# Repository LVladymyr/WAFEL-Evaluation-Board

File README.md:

# WAFEL EVAL BOARD

**Version:** 0.0.1

Evaluation board for the [Texas Instruments BQ76952](https://www.ti.com/product/BQ76952) multi-chemistry battery management IC. Designed to prototype and validate BMS firmware, cell monitoring, and protection circuits.

## Features

- BQ76952 multi-chemistry BMS IC (up to 16S, supports Li-ion, LiFePO4, NiMH)
- LM5164 synchronous buck regulator for on-board power supply
- TPS79333-EP ultra-low-noise LDO
- Charge and discharge MOSFET control path
- Automotive-grade blade fuse holder
- JST GH 17-pin battery connector
- Test points on key signals for bench debugging
- CI/CD pipeline: Gerbers, BOM, PDF schematic, 3D STEP, interactive BOM (iBOM)

## Hardware Overview

| Component | Part | Role |
|-----------|------|------|
| BMS IC | BQ76952 | Cell voltage/temperature monitoring, balancing, protection |
| Buck regulator | LM5164 | Steps down pack voltage to board supply rail |
| LDO | TPS79333-EP | Clean analog/digital supply from buck output |
| Charge FETs | — | Controlled by BQ76952 CHG/DSG pins |
| Connector | JST GH 17-pin | Battery pack interface |
| Fuse | Automotive blade | Pack-level overcurrent protection |

## Repository Structure

```
WAFEL_EVAL_BOARD/
├── *.kicad_pro        # KiCad project file
├── *.kicad_sch        # Schematic
├── *.kicad_pcb        # PCB layout
├── *.kicad_dru        # Design rules
├── fp-lib-table       # Footprint library table
├── sym-lib-table      # Symbol library table
├── .github/
│   └── workflows/     # CI/CD pipeline (KiBot)
└── README.md
```

## CI/CD & Manufacturing Outputs

Commits to `main` trigger a [KiBot](https://github.com/INTI-CMNB/KiBot) workflow via GitHub Actions that automatically generates:

- **Gerbers** — production-ready fabrication files
- **BOM** — bill of materials (CSV)
- **PDF** — schematic and PCB drawings
- **3D STEP** — mechanical model for enclosure design
- **iBOM** — interactive HTML BOM for assembly

Artifacts are attached to each workflow run.

## Getting Started

1. Install [KiCad 9.0](https://www.kicad.org/download/)
2. Clone this repository
3. Open the `.kicad_pro` file in KiCad

## License

Hardware design files are licensed under the **CERN Open Hardware Licence Version 2 – Strongly Reciprocal (CERN-OHL-S v2)**.
See [https://ohwr.org/cern_ohl_s_v2.txt](https://ohwr.org/cern_ohl_s_v2.txt) for the full license text.

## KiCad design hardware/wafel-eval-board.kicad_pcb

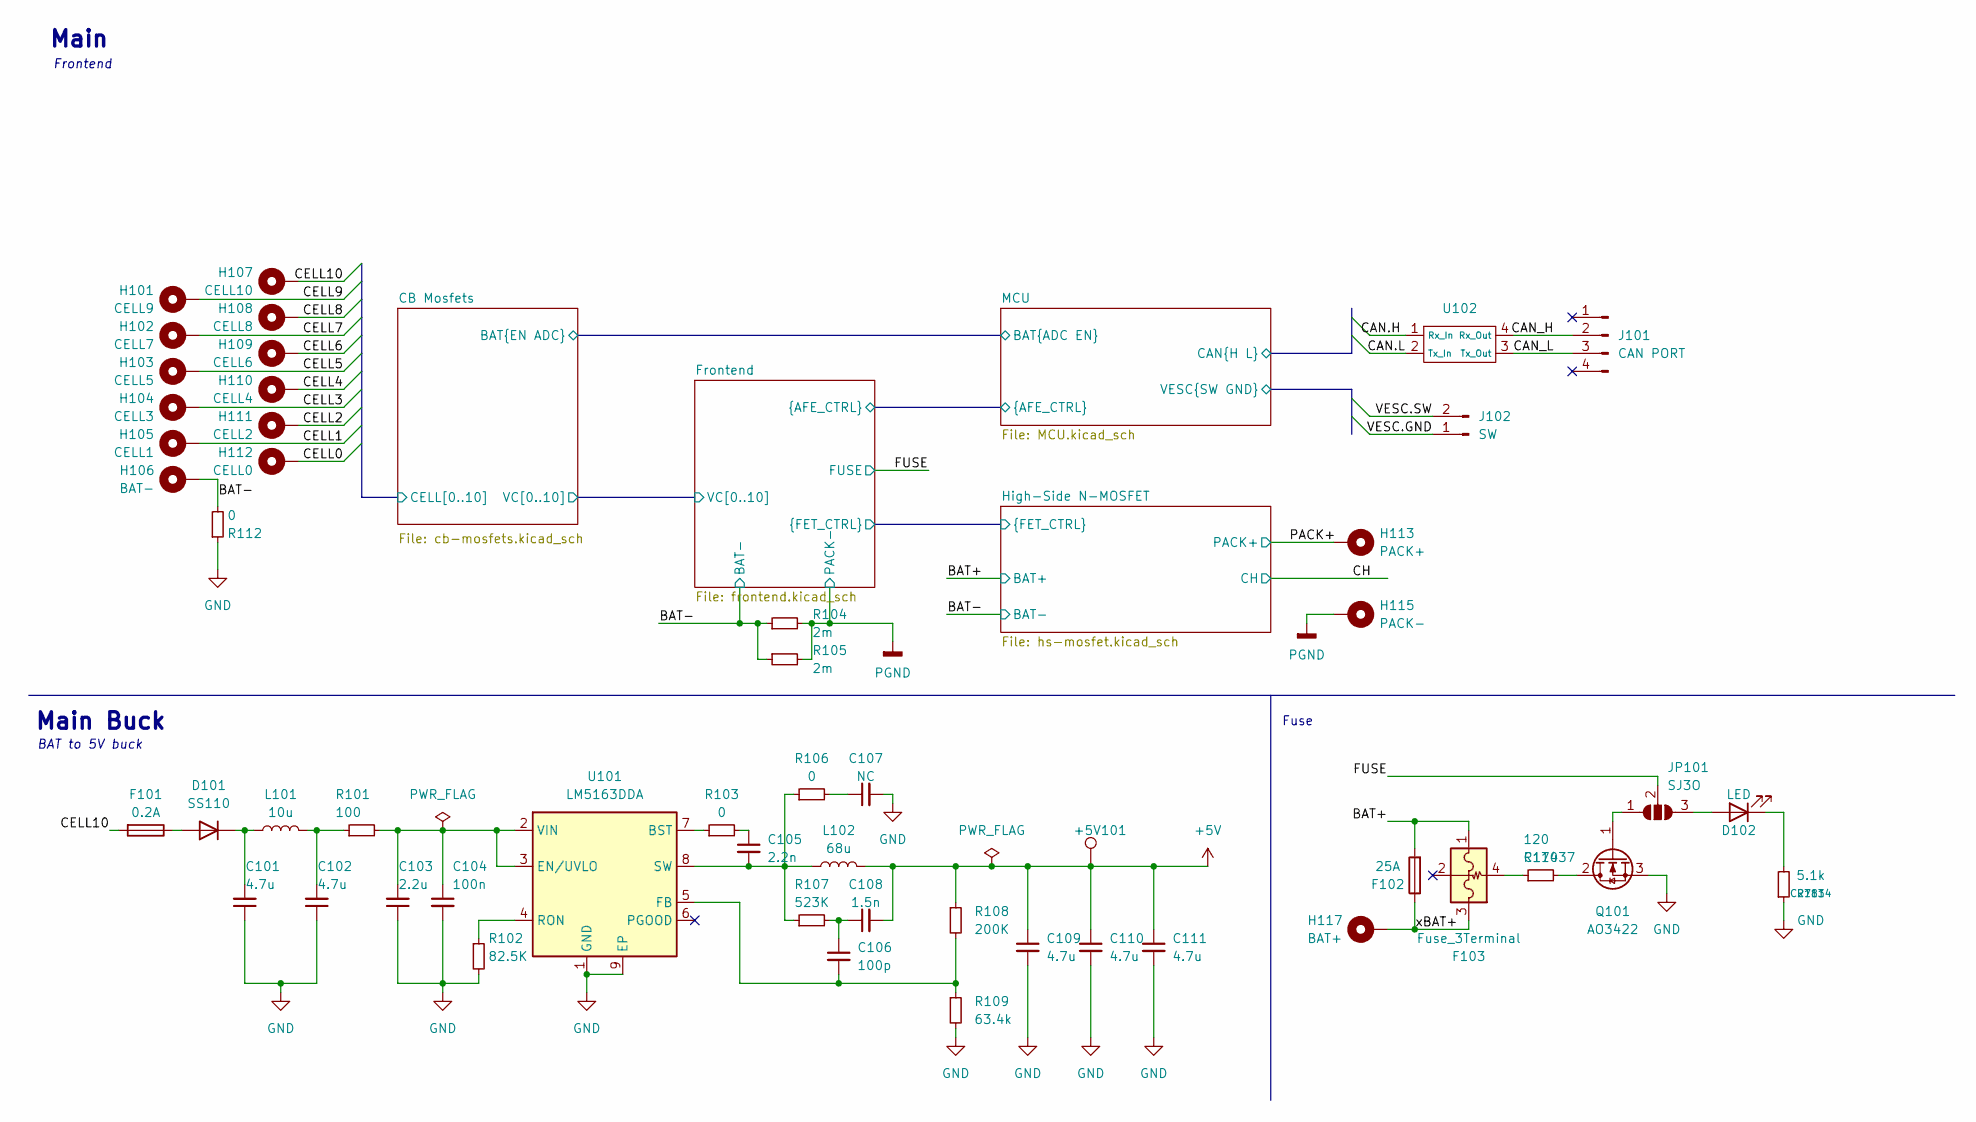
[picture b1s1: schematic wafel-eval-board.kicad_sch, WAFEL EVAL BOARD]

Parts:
+5V101: TestPoint; TestPoint_Pad_D1.0mm
C101, C102, C109, C110, C111: 4.7u; C_1206_3216Metric; LCSC C577211
C103: 2.2u; C_1206_3216Metric; LCSC C577211
C104: 100n; C_1206_3216Metric; LCSC C1945
C105: 2.2n; C_0603_1608Metric; LCSC C106861
C106: 100p; C_0603_1608Metric
C107: NC; C_0603_1608Metric
C108: 1.5n; C_0603_1608Metric
D101: SS110; D_SMA; LCSC C18199178
D102: LED; LED_0201_0603Metric
F101: 0.2A; Fuse_Littelfuse-NANO2-451_453; LCSC C178980
F102: 25A; Fuse_Littelfuse-NANO2-451_453; LCSC C178980
F103: Fuse_3Terminal; Fuse_ITV5432
H101: CELL9; MountingHole_3.2mm_M3_Pad
H102: CELL7; MountingHole_3.2mm_M3_Pad
H103: CELL5; MountingHole_3.2mm_M3_Pad
H104: CELL3; MountingHole_3.2mm_M3_Pad
H105: CELL1; MountingHole_3.2mm_M3_Pad
H106: BAT-; MountingHole_3.2mm_M3_Pad
H107: CELL10; MountingHole_3.2mm_M3_Pad
H108: CELL8; MountingHole_3.2mm_M3_Pad
H109: CELL6; MountingHole_3.2mm_M3_Pad
H110: CELL4; MountingHole_3.2mm_M3_Pad
H111: CELL2; MountingHole_3.2mm_M3_Pad
H112: CELL0; MountingHole_3.2mm_M3_Pad
H113: PACK+; MountingHole_3.2mm_M3_Pad
H115: PACK-; MountingHole_3.2mm_M3_Pad
H117: BAT+; MountingHole_3.2mm_M3_Pad
J101: CAN PORT; JST_PH_S4B-PH-K_1x04_P2.00mm_Horizontal
J102: SW; JST_PH_S2B-PH-K_1x02_P2.00mm_Horizontal
JP101: SJ3O; SolderJumper-3_P1.3mm_Open_Pad1.0x1.5mm
L101: 10u; L_KOHERelec_MDA7030; LCSC C2894721
L102: 68u; L_KOHERelec_MDA7030; LCSC C2894721
Q101: AO3422; SOT-23
R101: 100; R_0603_1608Metric; LCSC C17408
R102: 82.5K; R_0603_1608Metric; LCSC C3013228
R103: 0; R_0603_1608Metric; LCSC C17477
R104, R105: 2m; R_2512_6332Metric
R106, R112: 0; R_0603_1608Metric
R107: 523K; R_0603_1608Metric; LCSC C17742
R108: 200K; R_0603_1608Metric; LCSC C17539
R109: 63.4k; R_0603_1608Metric; LCSC C49654429
R110: 120; R_0603_1608Metric; LCSC C17437
R111: 5.1k; R_0603_1608Metric; LCSC C27834
U101: LM5163DDA; HSOP-8-1EP_3.9x4.9mm_P1.27mm_EP2.41x3.1mm_ThermalVias; LCSC C2873264
U102: poka-yoke_rxtx

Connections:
+5V: +5V101.1 (1_1), C108.2, C109.1, C110.1, C111.1, L102.2, R108.1; also elsewhere on the board
/BAT+: F102.2, F103.1; also elsewhere on the board
/BAT-: H106.1 (1_1), R104.1, R105.1, R112.2; also elsewhere on the board
/CAN_H: J101.2, U102.4 (Rx_Out)
/CAN_L: J101.3, U102.3 (Tx_Out)
/CB Mosfets/CELL0: H112.1 (1_1); also elsewhere on the board
/CB Mosfets/CELL1: H105.1 (1_1); also elsewhere on the board
/CB Mosfets/CELL2: H111.1 (1_1); also elsewhere on the board
/CB Mosfets/CELL3: H104.1 (1_1); also elsewhere on the board
/CB Mosfets/CELL4: H110.1 (1_1); also elsewhere on the board
/CB Mosfets/CELL5: H103.1 (1_1); also elsewhere on the board
/CB Mosfets/CELL6: H109.1 (1_1); also elsewhere on the board
/CB Mosfets/CELL7: H102.1 (1_1); also elsewhere on the board
/CB Mosfets/CELL8: H108.1 (1_1); also elsewhere on the board
/CB Mosfets/CELL9: H101.1 (1_1); also elsewhere on the board
/CB Mosfets/CELL10: F101.2, H107.1 (1_1); also elsewhere on the board
/FUSE: JP101.2 (C); also elsewhere on the board
/MCU/CAN.H: U102.1 (Rx_In); also elsewhere on the board
/MCU/CAN.L: U102.2 (Tx_In); also elsewhere on the board
/MCU/VESC.GND: J102.1; also elsewhere on the board
/MCU/VESC.SW: J102.2; also elsewhere on the board
/PACK+: H113.1 (1_1); also elsewhere on the board
/xBAT+: F102.1, F103.3, H117.1 (1_1)
GND: C101.1, C102.1, C103.1, C104.2, C107.2, C109.2, C110.2, C111.2, Q101.3 (S), R102.2, R109.2, R111.1, R112.1, U101.1 (GND), U101.9 (EP); also elsewhere on the board
unnamed: C102.2, L101.2, R101.1
unnamed: C105.1, R103.2
unnamed: C106.1, C108.1, R107.2
unnamed: C107.1, R106.2
unnamed: D101.2 (A), F101.1
unnamed: C101.2, D101.1 (K), L101.1
unnamed: D102.2 (A), JP101.3 (B)
unnamed: D102.1 (K), R111.2
unnamed: F103.4, R110.1
unnamed: JP101.1 (A), Q101.1 (G)
unnamed: Q101.2 (D), R110.2
unnamed: R103.1, U101.7 (BST)
unnamed: C103.2, C104.1, R101.2, U101.2 (VIN), U101.3 (EN/UVLO)
unnamed: C106.2, R108.2, R109.1, U101.5 (FB)
unnamed: R102.1, U101.4 (RON)
unnamed: C105.2, L102.1, R106.1, R107.1, U101.8 (SW)
PGND: H115.1 (1_1), R104.2, R105.2; also elsewhere on the board

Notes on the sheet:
Fuse
BAT to 5V buck
Frontend
Main Buck
Main

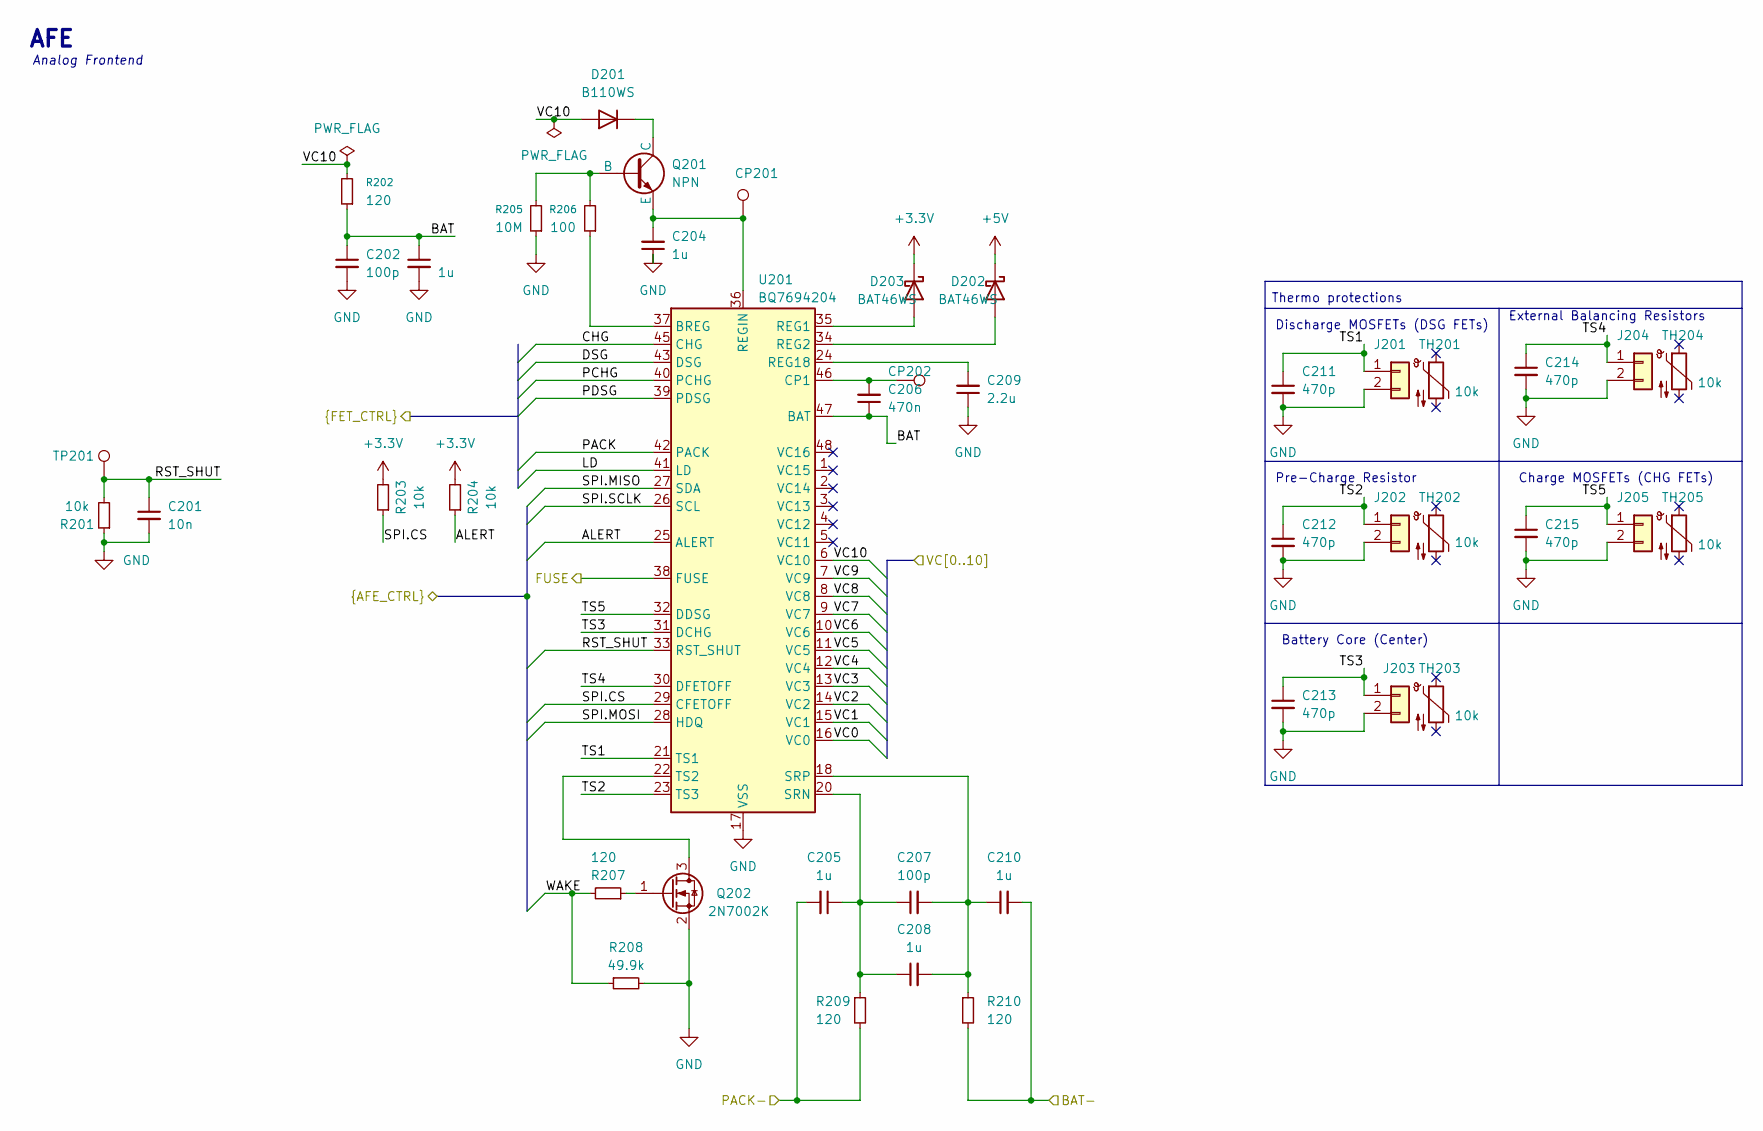
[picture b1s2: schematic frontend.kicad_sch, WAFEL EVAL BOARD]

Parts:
C201: 10n; C_0603_1608Metric
C202, C207: 100p; C_0603_1608Metric
C203: 1u; C_1206_3216Metric
C204, C205, C208, C210: 1u; C_0603_1608Metric
C206: 470n; C_0603_1608Metric
C209: 2.2u; C_1206_3216Metric; LCSC C577211
C211, C212, C213, C214, C215: 470p; C_0603_1608Metric
CP201, CP202: TestPoint; TestPoint_Pad_D1.0mm
D201: B110WS; D_SOD-323; LCSC C7461125
D202, D203: BAT46WS; D_SOD-323; LCSC C7502692
J201, J202, J203, J204, J205: Conn_01x02; PinHeader_1x02_P1.27mm_Vertical
Q201: NPN; SOT-23; Manufacturer_Part_Number FMMT458TA; Mouser Part Number 522-FMMT458TA
Q202: 2N7002K; SOT-23
R201, R203, R204: 10k; R_0603_1608Metric
R202, R207, R209, R210: 120; R_0603_1608Metric
R205: 10M; R_0603_1608Metric
R206: 100; R_0603_1608Metric
R208: 49.9k; R_0603_1608Metric
TH201, TH202, TH203, TH204, TH205: 10k; R_0603_1608Metric; LCSC C84036
TP201: TestPoint; TestPoint_Pad_D1.0mm
U201: BQ7694204; TQFP-48_7x7mm_P0.5mm

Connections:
+3.3V: D203.1 (K), R203.2, R204.2; also elsewhere on the board
+5V: D202.1 (K); also elsewhere on the board
/BAT-: C210.2, R210.2; also elsewhere on the board
/CB Mosfets/VC0: U201.16 (VC0); also elsewhere on the board
/CB Mosfets/VC1: U201.15 (VC1); also elsewhere on the board
/CB Mosfets/VC2: U201.14 (VC2); also elsewhere on the board
/CB Mosfets/VC3: U201.13 (VC3); also elsewhere on the board
/CB Mosfets/VC4: U201.12 (VC4); also elsewhere on the board
/CB Mosfets/VC5: U201.11 (VC5); also elsewhere on the board
/CB Mosfets/VC6: U201.10 (VC6); also elsewhere on the board
/CB Mosfets/VC7: U201.9 (VC7); also elsewhere on the board
/CB Mosfets/VC8: U201.8 (VC8); also elsewhere on the board
/CB Mosfets/VC9: U201.7 (VC9); also elsewhere on the board
/CB Mosfets/VC10: D201.2 (A), R202.2, U201.6 (VC10); also elsewhere on the board
/FUSE: U201.38 (FUSE); also elsewhere on the board
/Frontend/ALERT: R204.1, U201.25 (ALERT); also elsewhere on the board
/Frontend/BAT: C202.1, C203.1, C206.1, R202.1, U201.47 (BAT)
/Frontend/CHG: U201.45 (CHG); also elsewhere on the board
/Frontend/DSG: U201.43 (DSG); also elsewhere on the board
/Frontend/LD: U201.41 (LD); also elsewhere on the board
/Frontend/PACK: U201.42 (PACK); also elsewhere on the board
/Frontend/PCHG: U201.40 (PCHG); also elsewhere on the board
/Frontend/PDSG: U201.39 (PDSG); also elsewhere on the board
/Frontend/RST_SHUT: C201.1, R201.2, TP201.1 (1_1), U201.33 (RST_SHUT); also elsewhere on the board
/Frontend/SPI.CS: R203.1, U201.29 (CFETOFF); also elsewhere on the board
/Frontend/SPI.MISO: U201.27 (SDA); also elsewhere on the board
/Frontend/SPI.MOSI: U201.28 (HDQ); also elsewhere on the board
/Frontend/SPI.SCLK: U201.26 (SCL); also elsewhere on the board
/Frontend/TS1: C211.1, J201.1, U201.21 (TS1)
/Frontend/TS2: C212.1, J202.1, U201.23 (TS3)
/Frontend/TS3: C213.1, J203.1, U201.31 (DCHG)
/Frontend/TS4: C214.1, J204.1, U201.30 (DFETOFF); also elsewhere on the board
/Frontend/TS5: C215.1, J205.1, U201.32 (DDSG)
/Frontend/WAKE: R207.2, R208.1; also elsewhere on the board
GND: C201.2, C202.2, C203.2, C204.1, C209.1, C211.2, C212.2, C213.2, C215.2, J201.2, J202.2, J203.2, J204.2, J205.2, Q202.2 (S), R201.1, R205.1, R208.2, U201.17 (VSS); also elsewhere on the board
unnamed: D201.1 (K), Q201.1 (C)
unnamed: D202.2 (A), U201.34 (REG2)
unnamed: D203.2 (A), U201.35 (REG1)
unnamed: Q201.2 (B), R205.2, R206.2
unnamed: C204.2, CP201.1 (1_1), Q201.3 (E), U201.36 (REGIN)
unnamed: Q202.3 (D), U201.22 (TS2)
unnamed: Q202.1 (G), R207.1
unnamed: R206.1, U201.37 (BREG)
unnamed: C206.2, CP202.1 (1_1), U201.46 (CP1)
unnamed: C209.2, U201.24 (REG18)
unnamed: C205.1, C207.1, C208.1, R209.1, U201.20 (SRN)
unnamed: C207.2, C208.2, C210.1, R210.1, U201.18 (SRP)
PGND: C205.2, R209.2; also elsewhere on the board

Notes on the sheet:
Discharge MOSFETs (DSG FETs)
Analog Frontend
Battery Core (Center)
External Balancing Resistors
Charge MOSFETs (CHG FETs)
AFE
Pre-Charge Resistor
Thermo protections

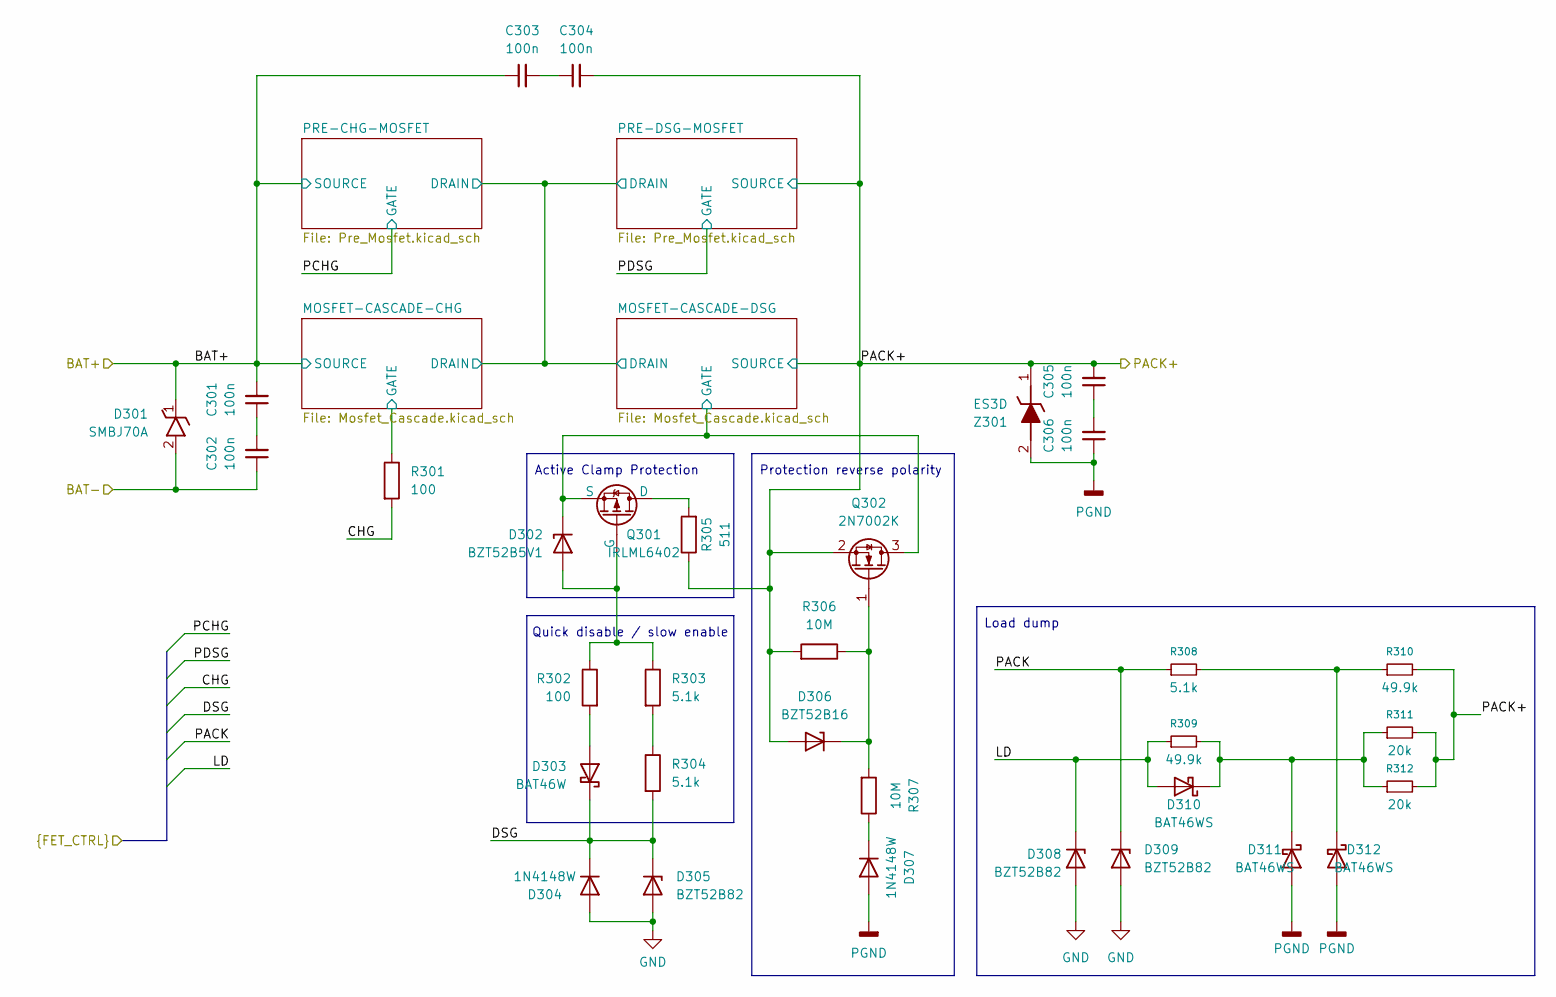
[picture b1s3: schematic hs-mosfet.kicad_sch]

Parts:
C301, C302, C303, C304, C305, C306: 100n; C_1206_3216Metric; Voltage 100V; LCSC C110255
D301: SMBJ70A; D_SMB; Manufacturer_Part_Number SMBJ70A
D302: BZT52B5V1; D_SOD-123
D303: BAT46W; D_SOD-123
D304, D307: 1N4148W; D_SOD-123
D305, D308, D309: BZT52B82; D_SOD-123F
D306: BZT52B16; D_SOD-123F
D310, D311, D312: BAT46WS; D_SOD-323; LCSC C7502692
Q301: IRLML6402; SOT-23
Q302: 2N7002K; SOT-23
R301, R302: 100; R_0603_1608Metric
R303, R304, R308: 5.1k; R_0603_1608Metric
R305: 511; R_0603_1608Metric
R306, R307: 10M; R_0603_1608Metric
R309, R310: 49.9k; R_0603_1608Metric
R311, R312: 20k; R_0603_1608Metric
Z301: ES3D; D_SMC; Manufacturer_Part_Number ES3D; Mouser Part Number 512-ES3D

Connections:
/BAT+: C301.2, C303.1, D301.1 (K); also elsewhere on the board
/BAT-: C302.1, D301.2 (A); also elsewhere on the board
/Frontend/CHG: R301.2; also elsewhere on the board
/Frontend/DSG: D303.1 (K), D304.1 (K), D305.1 (K), R304.2; also elsewhere on the board
/Frontend/LD: D308.1 (K), D310.2 (A), R309.1; also elsewhere on the board
/Frontend/PACK: D309.1 (K), R308.1; also elsewhere on the board
/High-Side N-MOSFET/MOSFET-CASCADE-CHG/GATE: R301.1; also elsewhere on the board
/High-Side N-MOSFET/MOSFET-CASCADE-DSG/GATE: D302.1 (K), Q301.3 (S), Q302.3 (D); also elsewhere on the board
/PACK+: C304.2, C305.2, D306.2 (A), Q302.2 (S), R305.1, R306.2, R310.2, R311.2, R312.2, Z301.1 (K); also elsewhere on the board
GND: D304.2 (A), D305.2 (A), D308.2 (A), D309.2 (A); also elsewhere on the board
unnamed: C301.1, C302.2
unnamed: C303.2, C304.1
unnamed: C305.1, C306.2
unnamed: D302.2 (A), Q301.2 (G), R302.1, R303.1
unnamed: D303.2 (A), R302.2
unnamed: D306.1 (K), Q302.1 (G), R306.1, R307.2
unnamed: D307.1 (K), R307.1
unnamed: D310.1 (K), D311.1 (K), R309.2, R311.1, R312.1
unnamed: D312.1 (K), R308.2, R310.1
unnamed: Q301.1 (D), R305.2
unnamed: R303.2, R304.1
PGND: C306.1, D307.2 (A), D311.2 (A), D312.2 (A), Z301.2 (A); also elsewhere on the board

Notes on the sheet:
Load dump
Protection reverse polarity
Quick disable / slow enable
Active Clamp Protection

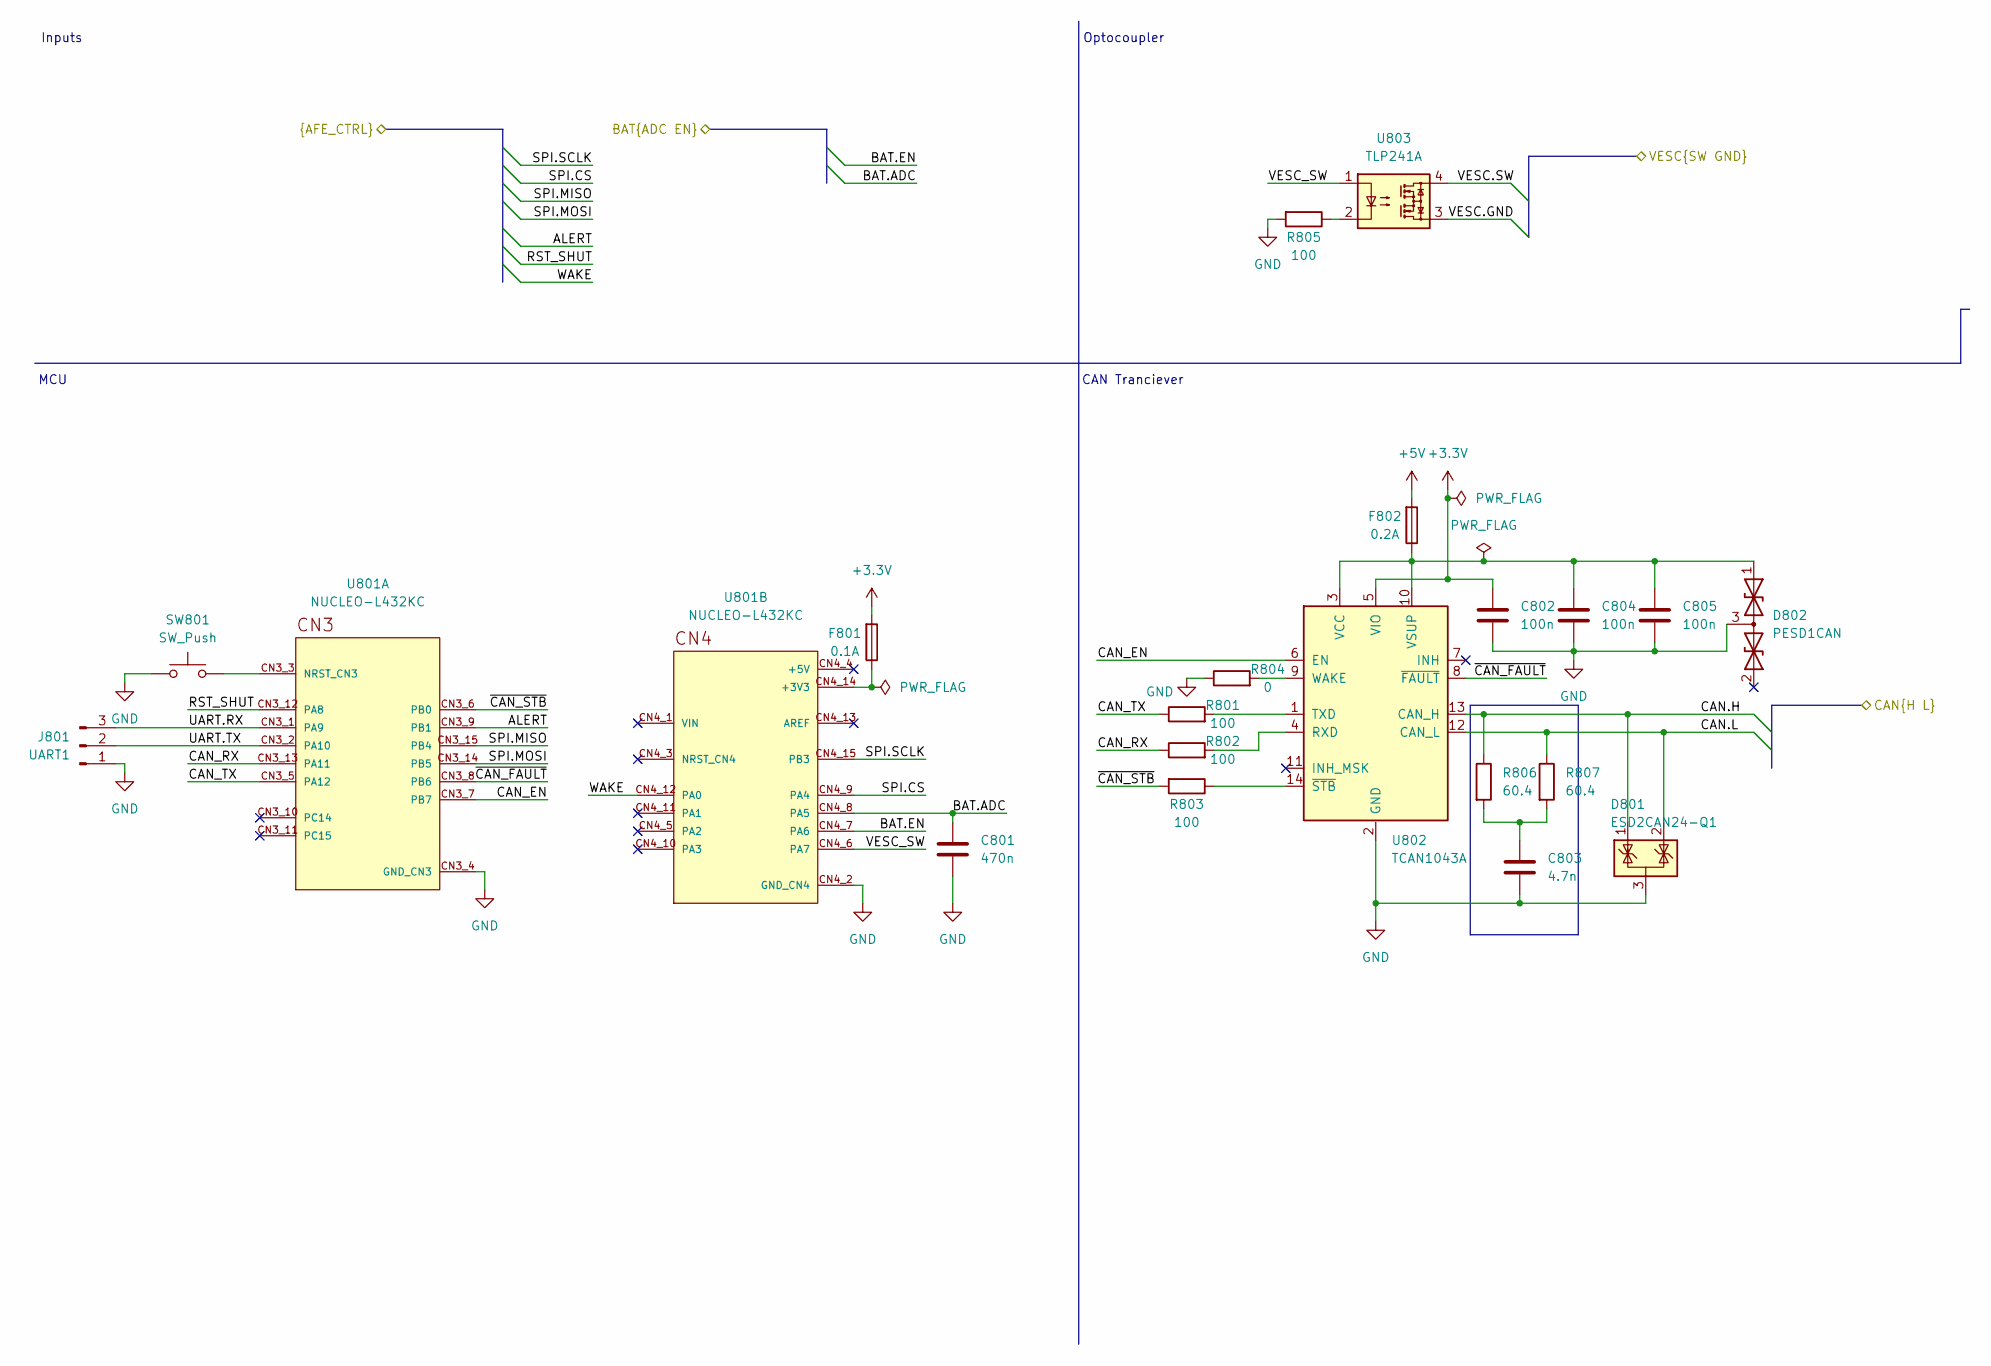
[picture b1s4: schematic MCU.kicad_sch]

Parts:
C801: 470n; C_0603_1608Metric
C802, C804, C805: 100n; C_0603_1608Metric; LCSC C14663
C803: 4.7n; C_0603_1608Metric; LCSC C14663
D801: ESD2CAN24-Q1; SOT-23
D802: PESD1CAN; SOT-23; LCSC C2687121
F801: 0.1A; Fuse_Littelfuse-NANO2-451_453; LCSC C178980
F802: 0.2A; Fuse_Littelfuse-NANO2-451_453; LCSC C178980
J801: UART1; JST_EH_B3B-EH-A_1x03_P2.50mm_Vertical
R801, R802, R803, R805: 100; R_0603_1608Metric; LCSC C22775
R804: 0; R_0603_1608Metric; LCSC C22775
R806, R807: 60.4; R_0603_1608Metric; LCSC C23090
SW801: SW_Push; SW_SPST_PTS810; LCSC C720477
U801: NUCLEO-L432KC; MODULE_NUCLEO-L432KC; PARTREV N/A
U802: TCAN1043A; SOIC-14_3.9x8.7mm_P1.27mm; MPN TCAN1043ADRQ1; LCSC C5215847
U803: TLP241A; DIP-4_W7.62mm

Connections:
+3.3V: C802.1, F801.2, U802.5 (VIO); also elsewhere on the board
+5V: F802.2; also elsewhere on the board
/CB Mosfets/BAT.ADC: C801.1, U801.CN4_8 (PA5); also elsewhere on the board
/CB Mosfets/BAT.EN: U801.CN4_7 (PA6); also elsewhere on the board
/Frontend/ALERT: U801.CN3_9 (PB1); also elsewhere on the board
/Frontend/RST_SHUT: U801.CN3_12 (PA8); also elsewhere on the board
/Frontend/SPI.CS: U801.CN4_9 (PA4); also elsewhere on the board
/Frontend/SPI.MISO: U801.CN3_15 (PB4); also elsewhere on the board
/Frontend/SPI.MOSI: U801.CN3_14 (PB5); also elsewhere on the board
/Frontend/SPI.SCLK: U801.CN4_15 (PB3); also elsewhere on the board
/Frontend/WAKE: U801.CN4_12 (PA0); also elsewhere on the board
/MCU/CAN.H: D801.1 (K), R806.1, U802.13 (CAN_H); also elsewhere on the board
/MCU/CAN.L: D801.2 (K), R807.1, U802.12 (CAN_L); also elsewhere on the board
/MCU/CAN_EN: U801.CN3_7 (PB7), U802.6 (EN)
/MCU/CAN_RX: R802.1, U801.CN3_13 (PA11)
/MCU/CAN_TX: R801.1, U801.CN3_5 (PA12)
/MCU/UART.RX: J801.3, U801.CN3_1 (PA9)
/MCU/UART.TX: J801.2, U801.CN3_2 (PA10)
/MCU/VESC.GND: U803.3; also elsewhere on the board
/MCU/VESC.SW: U803.4; also elsewhere on the board
/MCU/VESC_SW: U801.CN4_6 (PA7), U803.1
/MCU/~CAN_FAULT: U801.CN3_8 (PB6), U802.8 (~FAULT)
/MCU/~CAN_STB: R803.2, U801.CN3_6 (PB0)
GND: C801.2, C802.2, C803.2, C804.2, C805.2, D801.3 (A), D802.3 (common), J801.1, R804.1, R805.2, SW801.1, U801.CN3_4 (GND_CN3), U801.CN4_2 (GND_CN4), U802.2 (GND); also elsewhere on the board
unnamed: C803.1, R806.2, R807.2
unnamed: C804.1, C805.1, D802.1 (A1), F802.1, U802.3 (VCC), U802.10 (VSUP)
unnamed: R805.1, U803.2
unnamed: SW801.2, U801.CN3_3 (NRST_CN3)
unnamed: F801.1, U801.CN4_14 (+3V3)
unnamed: R802.2, U802.4 (RXD)
unnamed: R801.2, U802.1 (TXD)
unnamed: R804.2, U802.9 (WAKE)
unnamed: R803.1, U802.14 (~STB)

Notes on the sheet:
CAN Tranciever
MCU
Inputs
Optocoupler

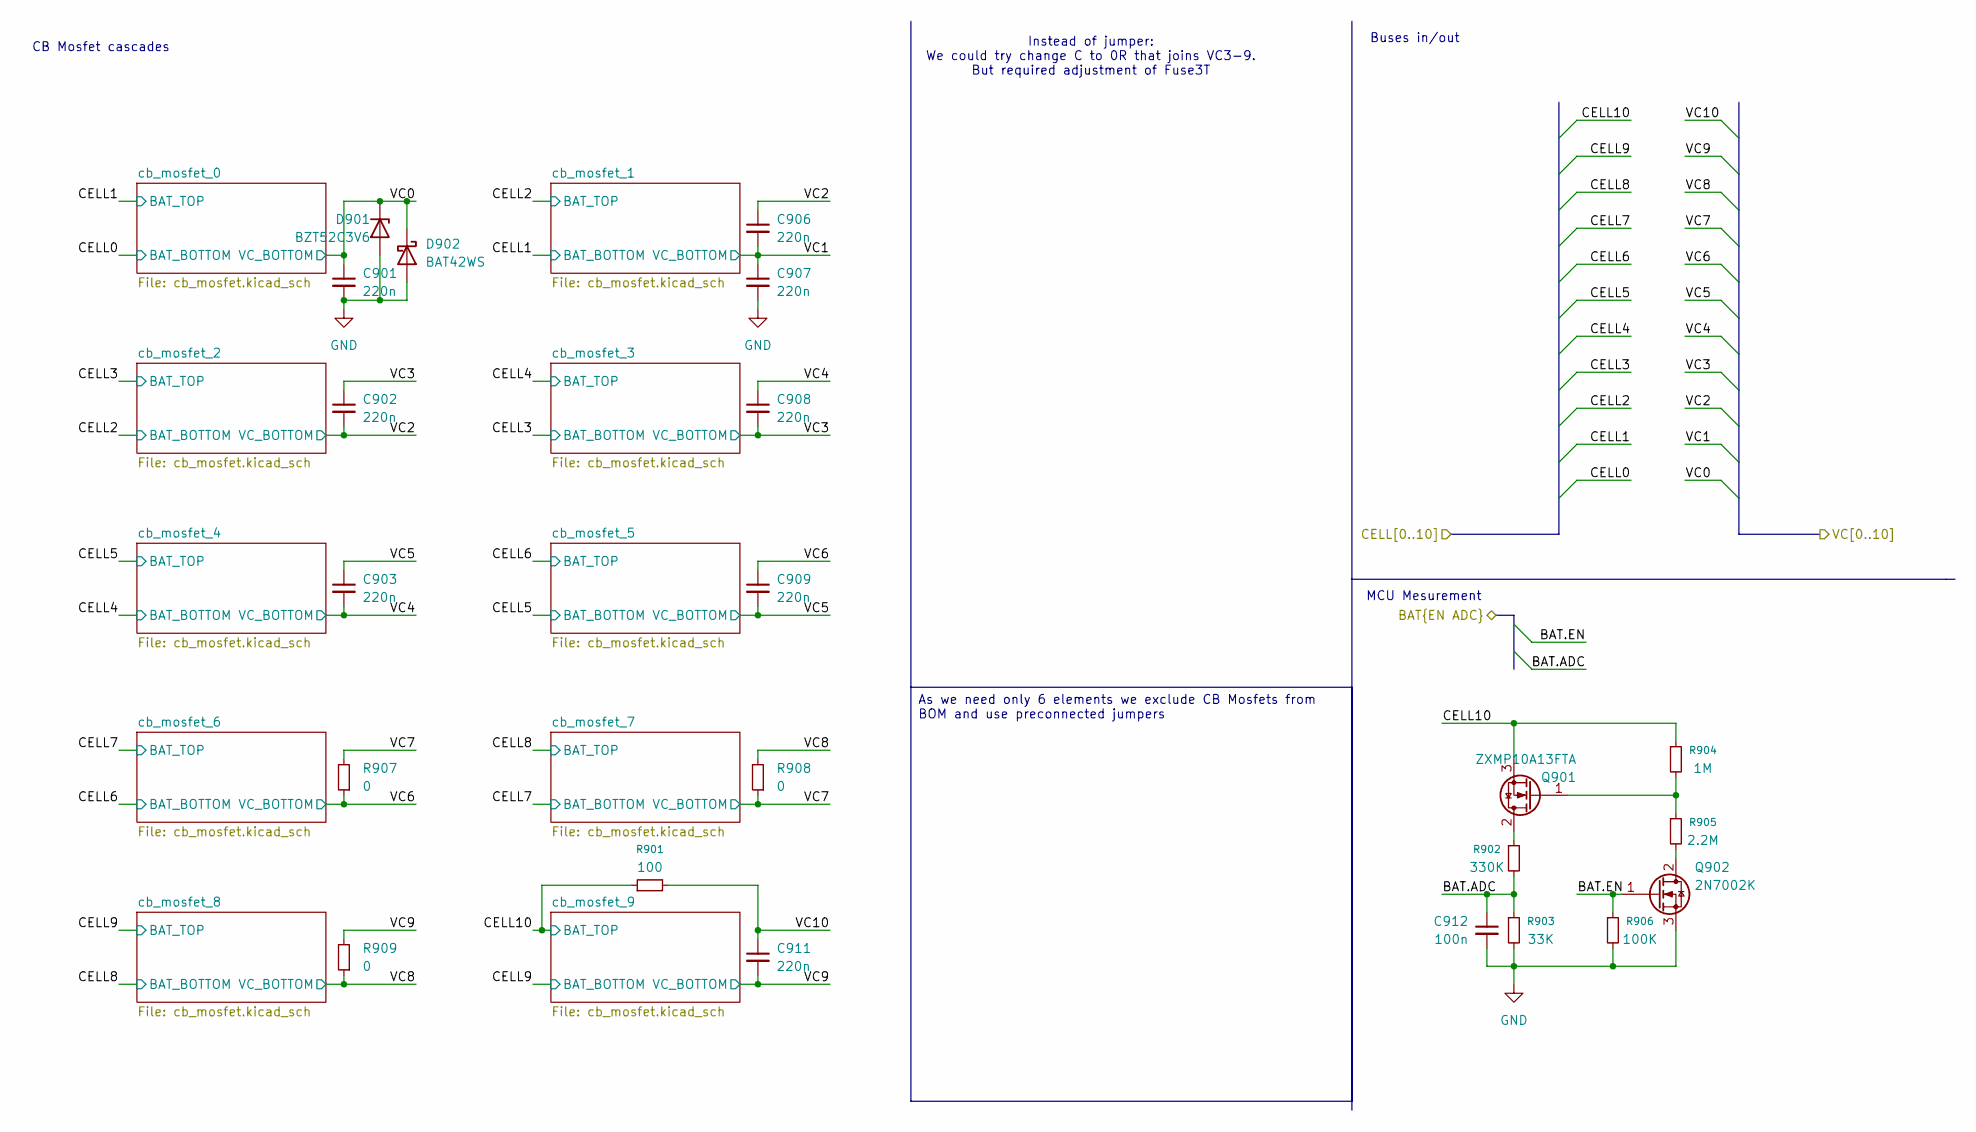
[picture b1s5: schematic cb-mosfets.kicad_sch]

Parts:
C901, C902, C903, C906, C907, C908, C909, C911: 220n; C_0603_1608Metric; LCSC C5378
C912: 100n; C_0603_1608Metric
D901: BZT52C3V6; D_SOD-123; LCSC C19077397
D902: BAT42WS; D_SOD-323F; LCSC C22466360
Q901: ZXMP10A13FTA; SOT-23
Q902: 2N7002K; SOT-23
R901: 100; R_0603_1608Metric; LCSC C17408
R902: 330K; R_0603_1608Metric; LCSC C17408
R903: 33K; R_0603_1608Metric; LCSC C17408
R904: 1M; R_0603_1608Metric; LCSC C17408
R905: 2.2M; R_0603_1608Metric; LCSC C17408
R906: 100K; R_0603_1608Metric; LCSC C17408
R907, R908, R909: 0; R_0603_1608Metric

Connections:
/CB Mosfets/BAT.ADC: C912.1, R902.2, R903.1; also elsewhere on the board
/CB Mosfets/BAT.EN: Q902.1 (G), R906.1; also elsewhere on the board
/CB Mosfets/CELL10: Q901.3 (S), R901.1, R904.1; also elsewhere on the board
/CB Mosfets/VC0: C901.1, D901.1 (K), D902.1 (K); also elsewhere on the board
/CB Mosfets/VC1: C906.2, C907.1; also elsewhere on the board
/CB Mosfets/VC2: C902.2, C906.1; also elsewhere on the board
/CB Mosfets/VC3: C902.1, C908.2; also elsewhere on the board
/CB Mosfets/VC4: C903.2, C908.1; also elsewhere on the board
/CB Mosfets/VC5: C903.1, C909.2; also elsewhere on the board
/CB Mosfets/VC6: C909.1, R907.1; also elsewhere on the board
/CB Mosfets/VC7: R907.2, R908.1; also elsewhere on the board
/CB Mosfets/VC8: R908.2, R909.1; also elsewhere on the board
/CB Mosfets/VC9: C911.2, R909.2; also elsewhere on the board
/CB Mosfets/VC10: C911.1, R901.2; also elsewhere on the board
GND: C901.2, C907.2, C912.2, D901.2 (A), D902.2 (A), Q902.3 (S), R903.2, R906.2; also elsewhere on the board
unnamed: Q901.2 (D), R902.1
unnamed: Q901.1 (G), R904.2, R905.1
unnamed: Q902.2 (D), R905.2

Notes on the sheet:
CB Mosfet cascades
Buses in/out
MCU Mesurement
Instead of jumper: We could try change C to 0R that joins VC3-9. But required adjustment of Fuse3T
As we need only 6 elements we exclude CB Mosfets from BOM and use preconnected jumpers

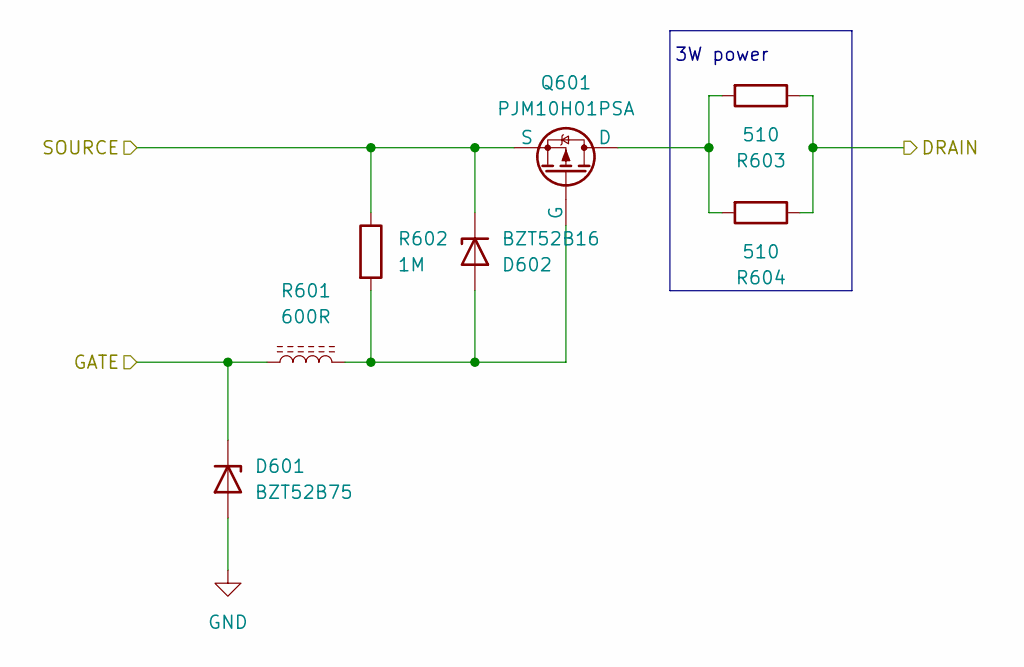
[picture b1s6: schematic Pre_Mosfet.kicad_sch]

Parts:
D601: BZT52B75; D_SOD-123F
D602: BZT52B16; D_SOD-123F
Q601: PJM10H01PSA; SOT-23; LCSC C2838029
R601: 600R; R_0603_1608Metric; LCSC C139183
R602: 1M; R_0603_1608Metric
R603, R604: 510; R_1206_3216Metric

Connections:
/BAT+: D602.1 (K), Q601.3 (S), R602.1; also elsewhere on the board
/Frontend/PCHG: D601.1 (K), R601.1; also elsewhere on the board
/High-Side N-MOSFET/MOSFET-CASCADE-CHG/DRAIN: R603.1, R604.1; also elsewhere on the board
GND: D601.2 (A); also elsewhere on the board
unnamed: D602.2 (A), Q601.2 (G), R601.2, R602.2
unnamed: Q601.1 (D), R603.2, R604.2

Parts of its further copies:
D701: BZT52B75; D_SOD-123F
D702: BZT52B16; D_SOD-123F
Q701: PJM10H01PSA; SOT-23; LCSC C2838029
R701: 600R; R_0603_1608Metric; LCSC C139183
R702: 1M; R_0603_1608Metric
R703, R704: 510; R_1206_3216Metric

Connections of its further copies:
/Frontend/PDSG: D701.1 (K), R701.1; also elsewhere on the board
/High-Side N-MOSFET/MOSFET-CASCADE-CHG/DRAIN: R703.1, R704.1; also elsewhere on the board
/PACK+: D702.1 (K), Q701.3 (S), R702.1; also elsewhere on the board
GND: D701.2 (A); also elsewhere on the board
unnamed: D702.2 (A), Q701.2 (G), R701.2, R702.2
unnamed: Q701.1 (D), R703.2, R704.2

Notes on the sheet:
3W power
